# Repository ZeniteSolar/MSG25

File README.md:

# MSG25
Módulo de sensoriamento geral para medição de 4 tensões e 3 temperaturas

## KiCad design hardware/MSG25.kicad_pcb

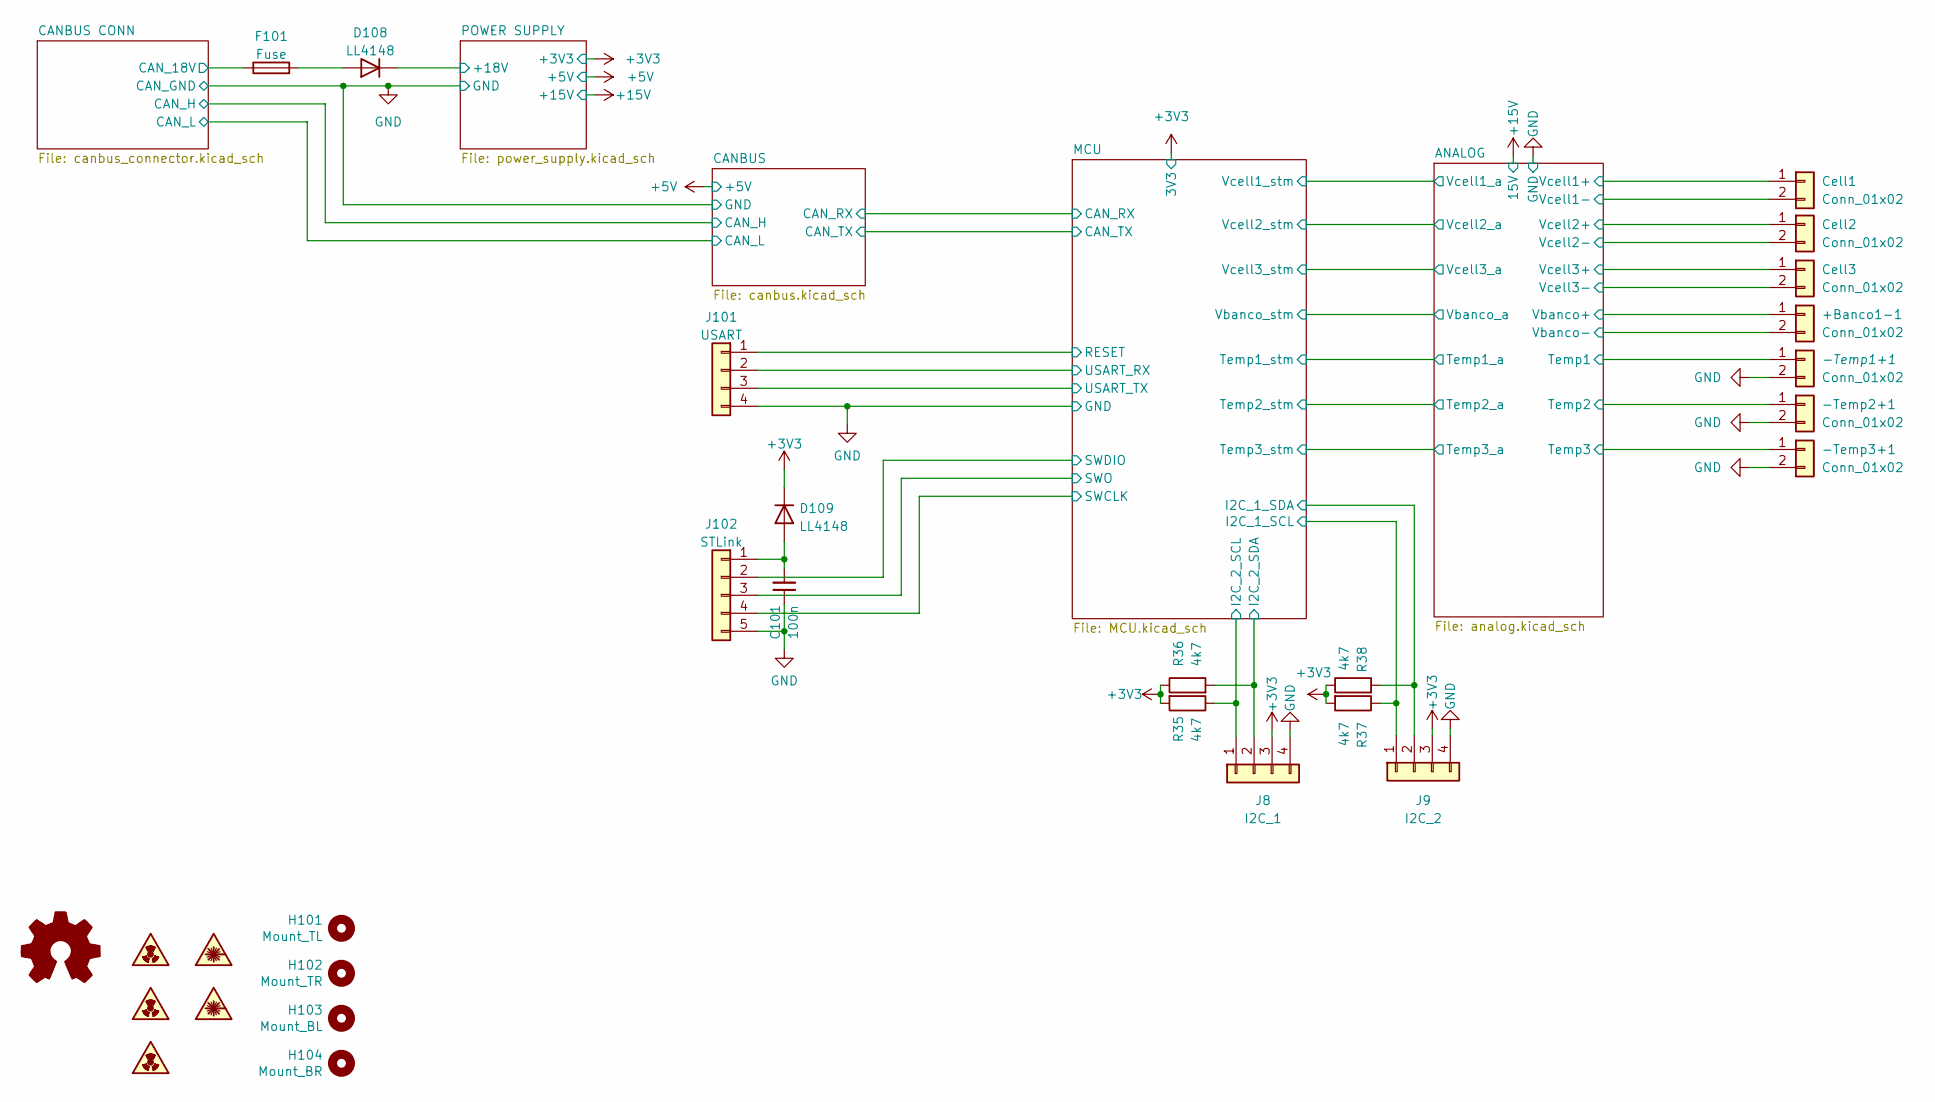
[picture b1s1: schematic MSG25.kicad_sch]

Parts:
+Banco1-1: Conn_01x02; TerminalBlock_bornier-2_P5.08mm
-Temp1+1, -Temp2+1, -Temp3+1: Conn_01x02; TerminalBlock_bornier-2_P5.08mm
C101: 100n; C_0603_1608Metric_Pad1.08x0.95mm_HandSolder
Cell1, Cell2, Cell3: Conn_01x02; TerminalBlock_bornier-2_P5.08mm
D108, D109: LL4148; D_MiniMELF
F101: Fuse; Fuse_1812_4532Metric_Pad1.30x3.40mm_HandSolder
H101: Mount_TL; MountingHole_3.2mm_M3
H102: Mount_TR; MountingHole_3.2mm_M3
H103: Mount_BL; MountingHole_3.2mm_M3
H104: Mount_BR; MountingHole_3.2mm_M3
J8: I2C_1; PinSocket_1x04_P2.54mm_Horizontal
J9: I2C_2; PinSocket_1x04_P2.54mm_Horizontal
J101: USART; PinSocket_1x04_P2.54mm_Horizontal
J102: STLink; PinSocket_1x05_P2.54mm_Vertical
LOGO101: Logo_Open_Hardware_Small; OSHW-Logo2_7.3x6mm_SilkScreen
R35, R36, R37, R38: 4k7; R_0805_2012Metric_Pad1.20x1.40mm_HandSolder
SYM101, SYM102: SYM_Radioactive_Radiation_Small; symbol_logoZenite
SYM103: SYM_Radioactive_Radiation_Small; symbol_naolavar
SYM104, SYM105: SYM_LASER_Small; synbol_logoifsc

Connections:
+3V3: D109.1 (K), J8.3, J9.3, R35.2, R36.1, R37.2, R38.1; also elsewhere on the board
/ANALOG/Temp1: -Temp1+1.1; also elsewhere on the board
/ANALOG/Temp2: -Temp2+1.1; also elsewhere on the board
/ANALOG/Temp3: -Temp3+1.1; also elsewhere on the board
/ANALOG/Vbanco+: +Banco1-1.1; also elsewhere on the board
/ANALOG/Vbanco-: +Banco1-1.2; also elsewhere on the board
/ANALOG/Vcell1+: Cell1.1; also elsewhere on the board
/ANALOG/Vcell1-: Cell1.2; also elsewhere on the board
/ANALOG/Vcell2+: Cell2.1; also elsewhere on the board
/ANALOG/Vcell2-: Cell2.2; also elsewhere on the board
/ANALOG/Vcell3+: Cell3.1; also elsewhere on the board
/ANALOG/Vcell3-: Cell3.2; also elsewhere on the board
/CANBUS CONN/CAN_18V: F101.1; also elsewhere on the board
/MCU/I2C_1_SCL: J9.1, R37.1; also elsewhere on the board
/MCU/I2C_1_SDA: J9.2, R38.2; also elsewhere on the board
/MCU/I2C_2_SCL: J8.1, R35.1; also elsewhere on the board
/MCU/I2C_2_SDA: J8.2, R36.2; also elsewhere on the board
/MCU/RESET: J101.1; also elsewhere on the board
/MCU/SWCLK: J102.4; also elsewhere on the board
/MCU/SWDIO: J102.2; also elsewhere on the board
/MCU/SWO: J102.3; also elsewhere on the board
/MCU/USART_RX: J101.2; also elsewhere on the board
/MCU/USART_TX: J101.3; also elsewhere on the board
/POWER SUPPLY/+18V: D108.1 (K); also elsewhere on the board
GND: -Temp1+1.2, -Temp2+1.2, -Temp3+1.2, C101.1, J8.4, J9.4, J101.4, J102.5; also elsewhere on the board
unnamed: D108.2 (A), F101.2
unnamed: C101.2, D109.2 (A), J102.1

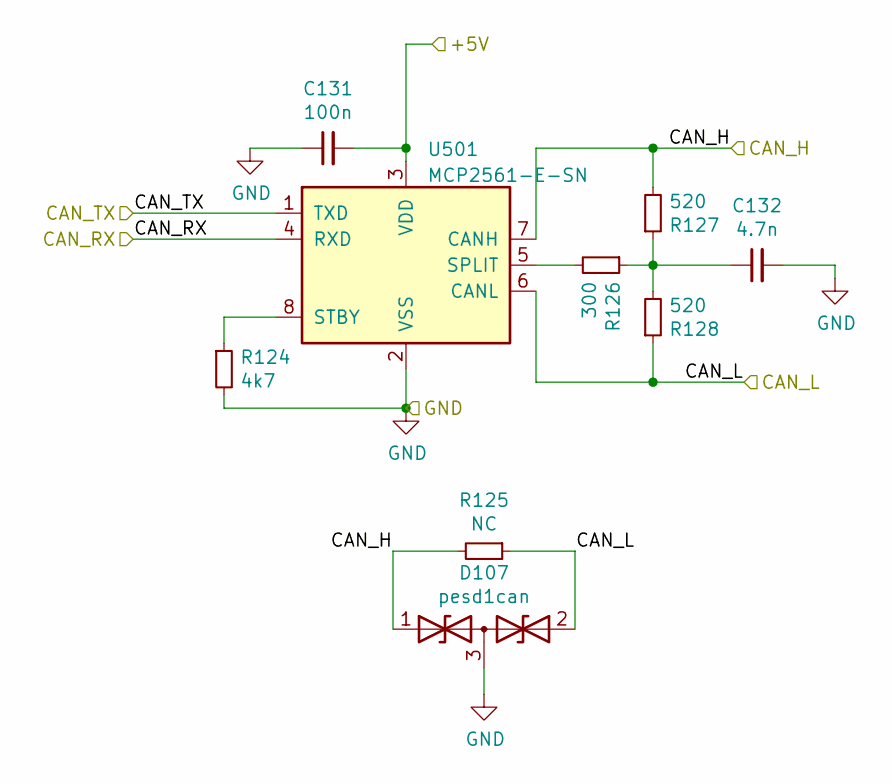
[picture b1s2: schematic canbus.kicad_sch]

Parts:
C131: 100n; C_0603_1608Metric_Pad1.08x0.95mm_HandSolder
C132: 4.7n; C_0603_1608Metric_Pad1.08x0.95mm_HandSolder
D107: pesd1can; SOT-23
R124: 4k7; R_0603_1608Metric_Pad0.98x0.95mm_HandSolder
R125: NC; R_0603_1608Metric_Pad0.98x0.95mm_HandSolder
R126: 300; R_0603_1608Metric_Pad0.98x0.95mm_HandSolder
R127, R128: 520; R_0603_1608Metric_Pad0.98x0.95mm_HandSolder
U501: MCP2561-E-SN; SOIC-8_3.9x4.9mm_P1.27mm

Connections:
+5V: C131.2, U501.3 (VDD); also elsewhere on the board
/CANBUS CONN/CAN_H: D107.1 (A1), R125.2, R127.2, U501.7 (CANH); also elsewhere on the board
/CANBUS CONN/CAN_L: D107.2 (A2), R125.1, R128.1, U501.6 (CANL); also elsewhere on the board
/CANBUS/CAN_RX: U501.4 (RXD); also elsewhere on the board
/CANBUS/CAN_TX: U501.1 (TXD); also elsewhere on the board
GND: C131.1, C132.2, D107.3 (common), R124.2, U501.2 (VSS); also elsewhere on the board
unnamed: C132.1, R126.1, R127.1, R128.2
unnamed: R126.2, U501.5 (SPLIT)
unnamed: R124.1, U501.8 (STBY)

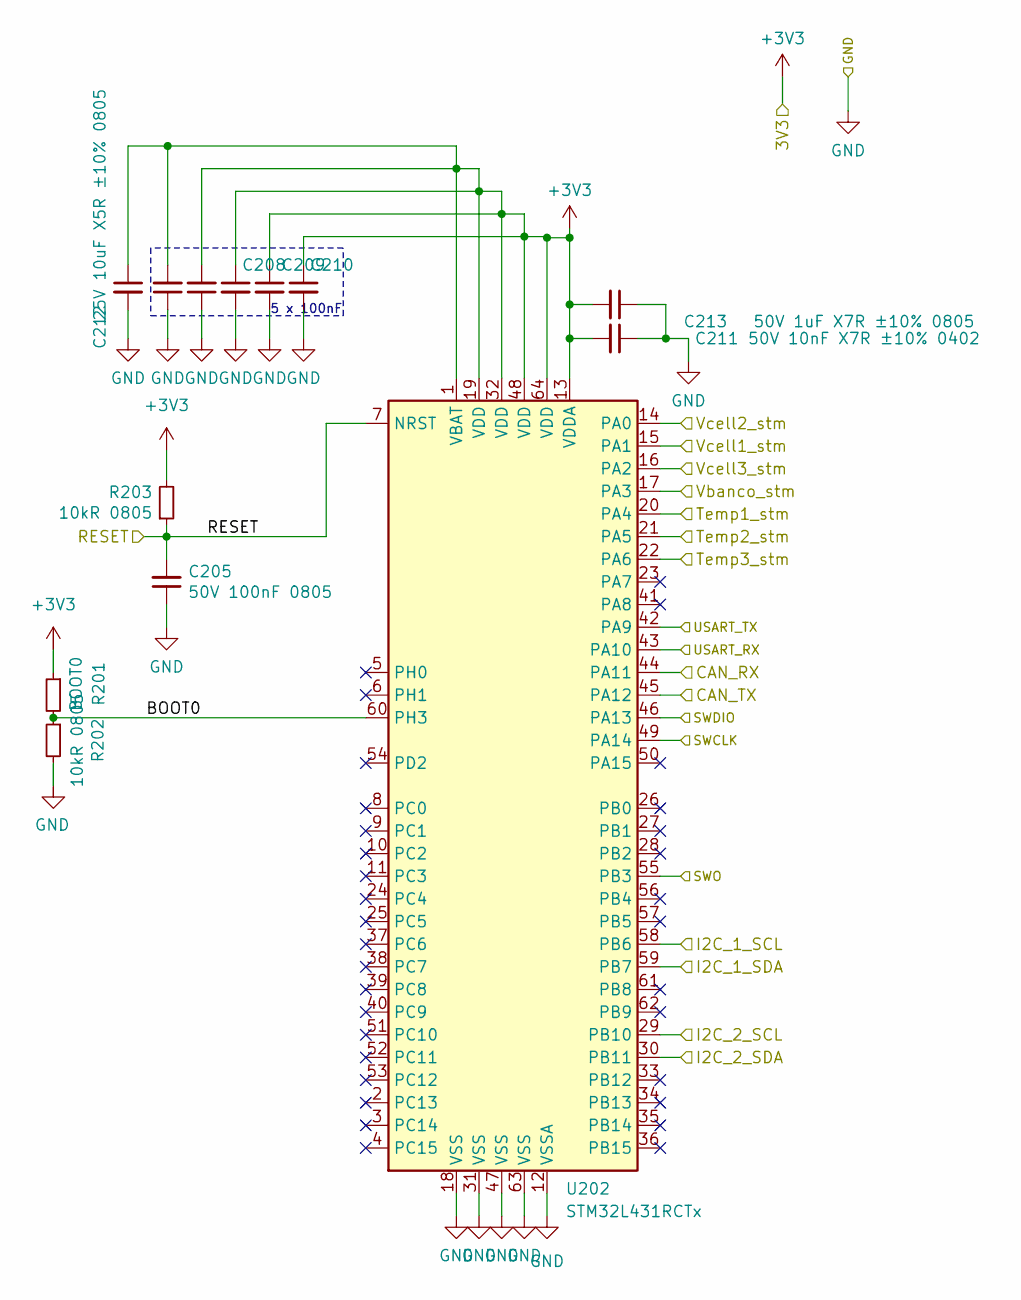
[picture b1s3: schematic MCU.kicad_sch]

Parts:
C205, C206, C207: 50V 100nF 0805; C_0805_2012Metric_Pad1.18x1.45mm_HandSolder
C208, C209, C210: 50V 100nF X7R ±10% 0402; C_0402_1005Metric_Pad0.74x0.62mm_HandSolder
C211: 50V 10nF X7R ±10% 0402; C_0402_1005Metric_Pad0.74x0.62mm_HandSolder
C212: 25V 10uF X5R ±10% 0805; C_0805_2012Metric_Pad1.18x1.45mm_HandSolder
C213: 50V 1uF X7R ±10% 0805; C_0805_2012Metric_Pad1.18x1.45mm_HandSolder
R201: BOOT0; R_0402_1005Metric
R202, R203: 10kR 0805; R_0805_2012Metric_Pad1.20x1.40mm_HandSolder
U202: STM32L431RCTx; LQFP-64_10x10mm_P0.5mm

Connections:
+3V3: C206.2, C207.2, C208.1, C209.1, C210.1, C211.2, C212.1, C213.2, R201.1, R203.2, U202.1 (VBAT), U202.13 (VDDA), U202.19 (VDD), U202.32 (VDD), U202.48 (VDD), U202.64 (VDD); also elsewhere on the board
/ANALOG/Temp1_a: U202.20 (PA4); also elsewhere on the board
/ANALOG/Temp2_a: U202.21 (PA5); also elsewhere on the board
/ANALOG/Temp3_a: U202.22 (PA6); also elsewhere on the board
/ANALOG/Vbanco_a: U202.17 (PA3); also elsewhere on the board
/ANALOG/Vcell1_a: U202.15 (PA1); also elsewhere on the board
/ANALOG/Vcell2_a: U202.14 (PA0); also elsewhere on the board
/ANALOG/Vcell3_a: U202.16 (PA2); also elsewhere on the board
/CANBUS/CAN_RX: U202.44 (PA11); also elsewhere on the board
/CANBUS/CAN_TX: U202.45 (PA12); also elsewhere on the board
/MCU/BOOT0: R201.2, R202.1, U202.60 (PH3)
/MCU/I2C_1_SCL: U202.58 (PB6); also elsewhere on the board
/MCU/I2C_1_SDA: U202.59 (PB7); also elsewhere on the board
/MCU/I2C_2_SCL: U202.29 (PB10); also elsewhere on the board
/MCU/I2C_2_SDA: U202.30 (PB11); also elsewhere on the board
/MCU/RESET: C205.2, R203.1, U202.7 (NRST); also elsewhere on the board
/MCU/SWCLK: U202.49 (PA14); also elsewhere on the board
/MCU/SWDIO: U202.46 (PA13); also elsewhere on the board
/MCU/SWO: U202.55 (PB3); also elsewhere on the board
/MCU/USART_RX: U202.43 (PA10); also elsewhere on the board
/MCU/USART_TX: U202.42 (PA9); also elsewhere on the board
GND: C205.1, C206.1, C207.1, C208.2, C209.2, C210.2, C211.1, C212.2, C213.1, R202.2, U202.12 (VSSA), U202.18 (VSS), U202.31 (VSS), U202.47 (VSS), U202.63 (VSS); also elsewhere on the board

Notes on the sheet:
5 x 100nF

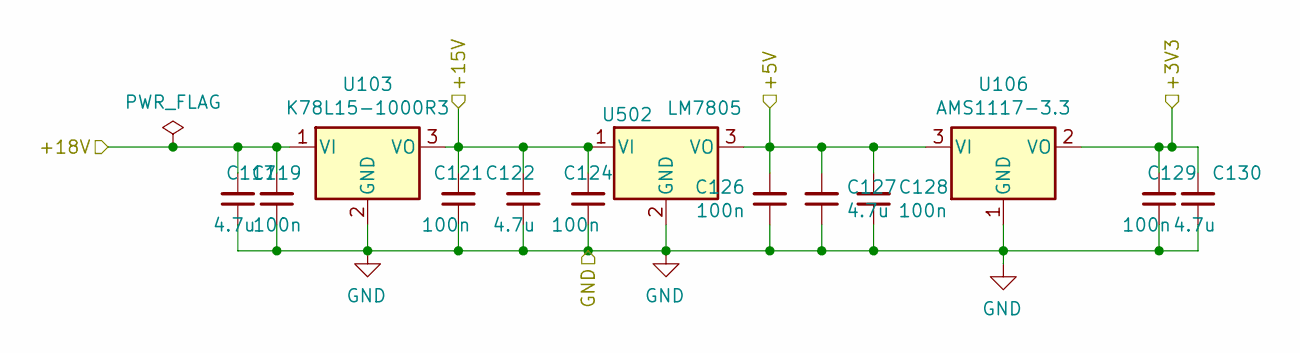
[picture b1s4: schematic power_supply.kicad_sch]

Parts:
C117, C122, C127, C130: 4.7u; C_1206_3216Metric_Pad1.33x1.80mm_HandSolder
C119, C121, C124, C126, C128, C129: 100n; C_0603_1608Metric_Pad1.08x0.95mm_HandSolder
U103: K78L15-1000R3; TO-220-3_Horizontal_TabDown
U106: AMS1117-3.3; SOT-223-3_TabPin2
U502: LM7805; TO-220-3_Horizontal_TabDown

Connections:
+3V3: C129.2, C130.2, U106.2 (VO); also elsewhere on the board
+5V: C126.2, C127.2, C128.2, U106.3 (VI), U502.3 (VO); also elsewhere on the board
+15V: C121.2, C122.2, C124.2, U103.3 (VO), U502.1 (VI); also elsewhere on the board
/POWER SUPPLY/+18V: C117.2, C119.2, U103.1 (VI); also elsewhere on the board
GND: C117.1, C119.1, C121.1, C122.1, C124.1, C126.1, C127.1, C128.1, C129.1, C130.1, U103.2 (GND), U106.1 (GND), U502.2 (GND); also elsewhere on the board

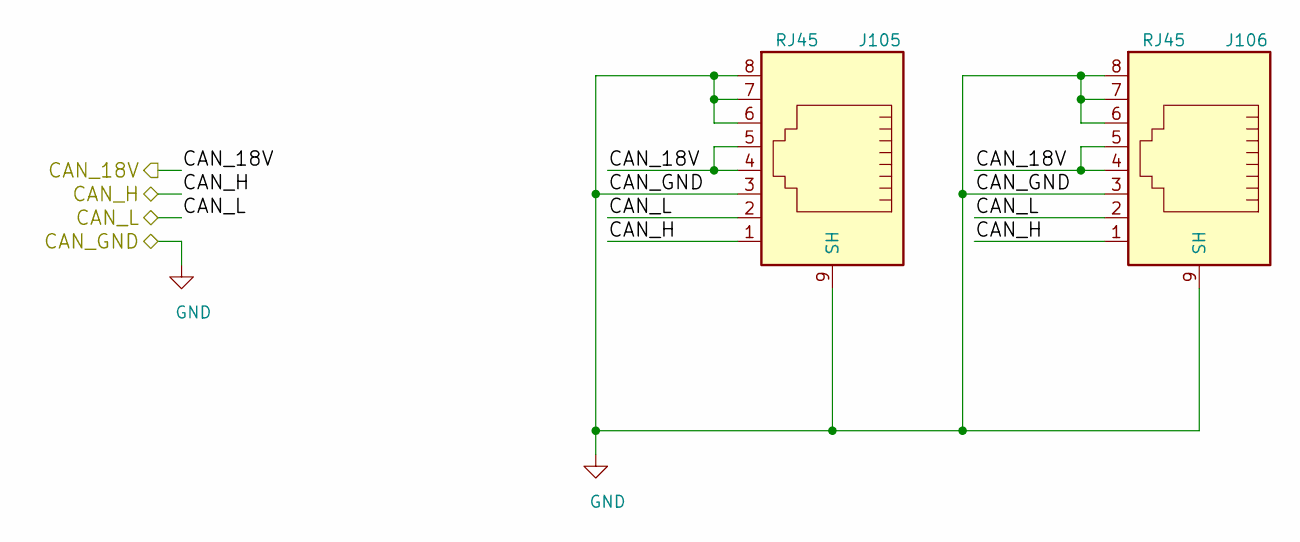
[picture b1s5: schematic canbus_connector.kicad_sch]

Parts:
J105, J106: RJ45; RJ45_YH59_01

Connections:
/CANBUS CONN/CAN_18V: J105.4, J105.5, J106.4, J106.5; also elsewhere on the board
/CANBUS CONN/CAN_H: J105.1, J106.1; also elsewhere on the board
/CANBUS CONN/CAN_L: J105.2, J106.2; also elsewhere on the board
GND: J105.3, J105.6, J105.7, J105.8, J105.9 (SH), J106.3, J106.6, J106.7, J106.8, J106.9 (SH); also elsewhere on the board

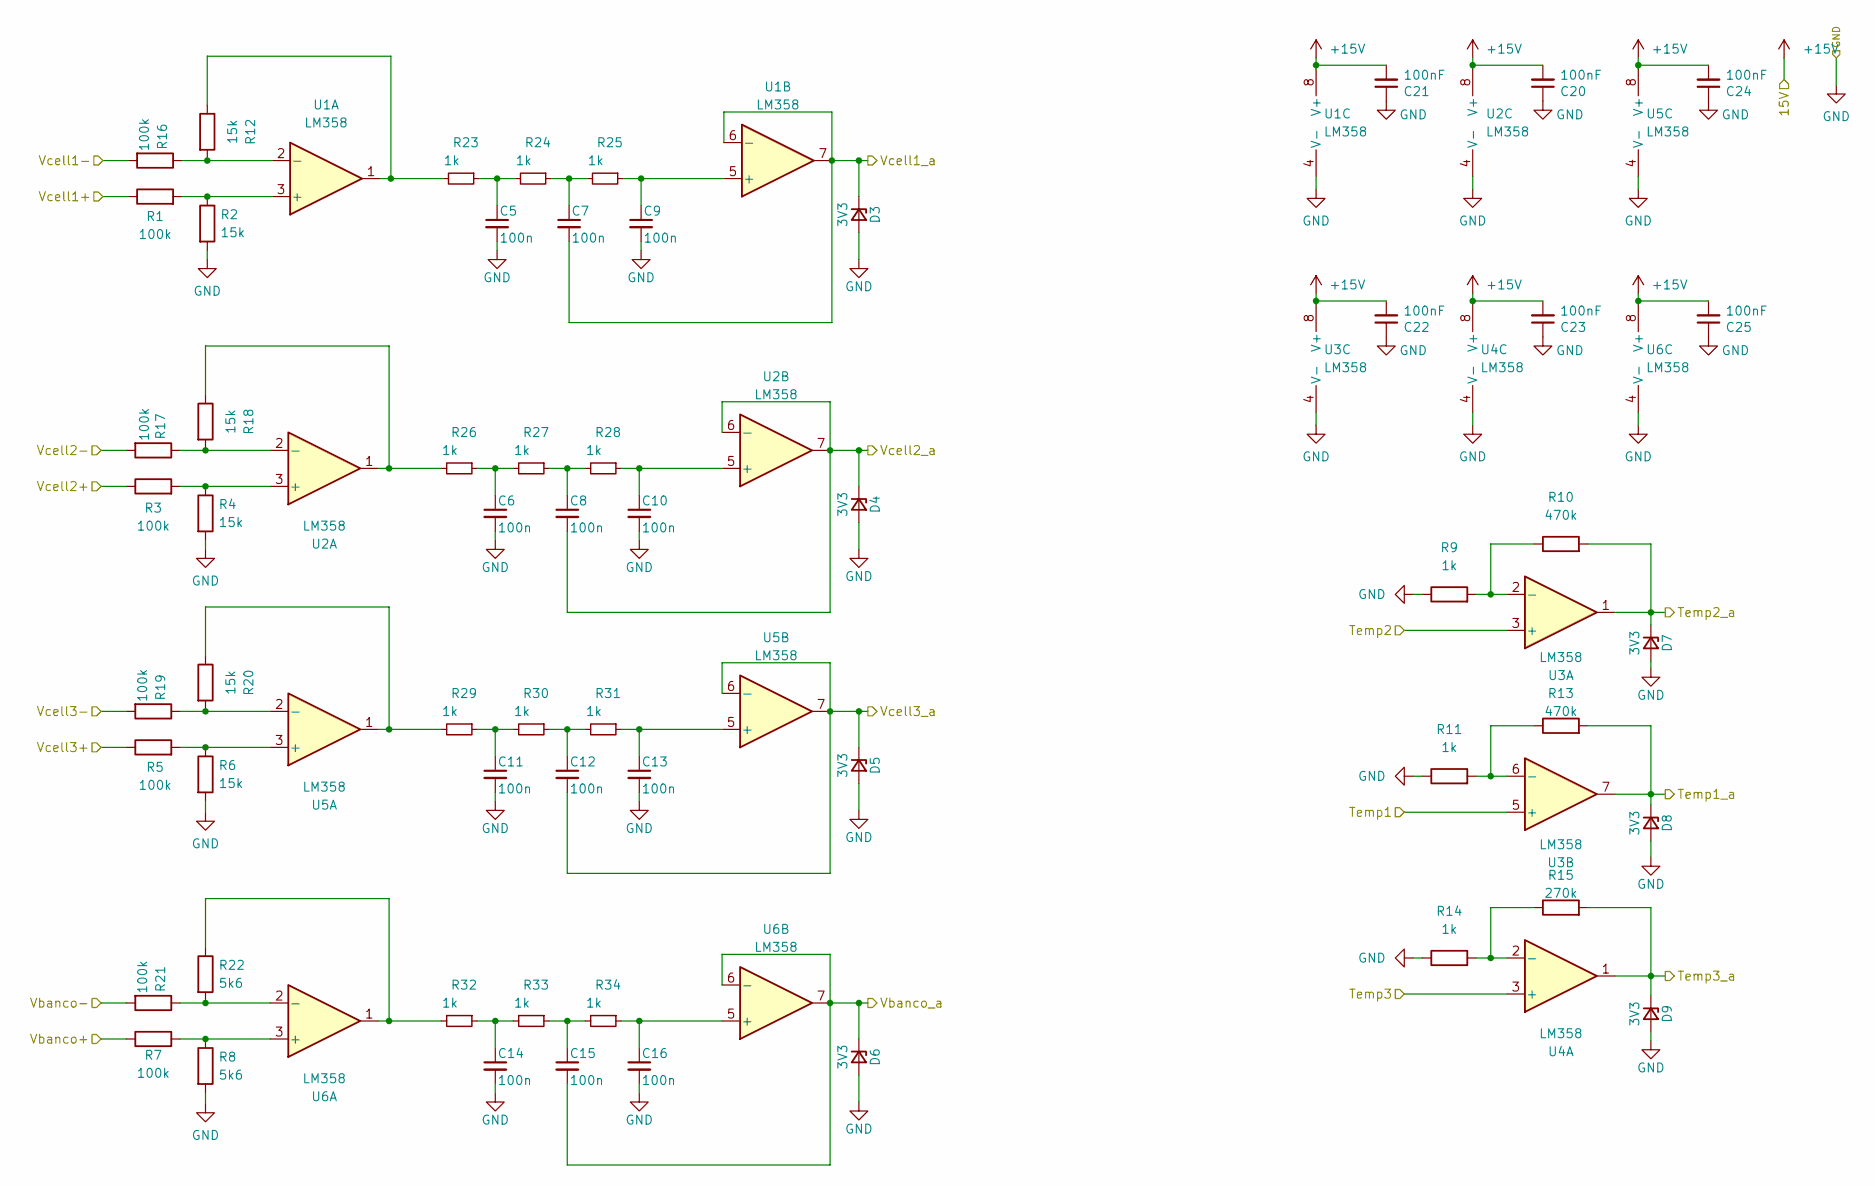
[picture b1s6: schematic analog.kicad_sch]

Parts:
C5, C6, C7, C8, C9, C10, C11, C12, C13, C14, C15, C16: 100n; C_0805_2012Metric_Pad1.18x1.45mm_HandSolder
C20, C21, C22, C23, C24, C25: 100nF; C_0805_2012Metric_Pad1.18x1.45mm_HandSolder
D3, D4, D5, D6, D7, D8, D9: 3V3; D_MiniMELF
R1, R3, R5, R7, R16, R17, R19, R21: 100k; R_0805_2012Metric_Pad1.20x1.40mm_HandSolder
R2, R4, R6, R12, R18, R20: 15k; R_0805_2012Metric_Pad1.20x1.40mm_HandSolder
R8, R22: 5k6; R_0805_2012Metric_Pad1.20x1.40mm_HandSolder
R9, R11, R14, R23, R24, R25, R26, R27, R28, R29, R30, R31, R32, R33, R34: 1k; R_0805_2012Metric_Pad1.20x1.40mm_HandSolder
R10, R13: 470k; R_0805_2012Metric_Pad1.20x1.40mm_HandSolder
R15: 270k; R_0805_2012Metric_Pad1.20x1.40mm_HandSolder
U1, U2, U3, U4, U5, U6: LM358; SOIC-8_3.9x4.9mm_P1.27mm

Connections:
+15V: C20.2, C21.2, C22.2, C23.2, C24.2, C25.2, U1.8 (V+), U2.8 (V+), U3.8 (V+), U4.8 (V+), U5.8 (V+), U6.8 (V+); also elsewhere on the board
/ANALOG/Temp1: U3.5 (+); also elsewhere on the board
/ANALOG/Temp1_a: D8.1 (K), R13.2, U3.7; also elsewhere on the board
/ANALOG/Temp2: U3.3 (+); also elsewhere on the board
/ANALOG/Temp2_a: D7.1 (K), R10.2, U3.1; also elsewhere on the board
/ANALOG/Temp3: U4.3 (+); also elsewhere on the board
/ANALOG/Temp3_a: D9.1 (K), R15.2, U4.1; also elsewhere on the board
/ANALOG/Vbanco+: R7.1; also elsewhere on the board
/ANALOG/Vbanco-: R21.2; also elsewhere on the board
/ANALOG/Vbanco_a: C15.2, D6.1 (K), U6.6 (-), U6.7; also elsewhere on the board
/ANALOG/Vcell1+: R1.1; also elsewhere on the board
/ANALOG/Vcell1-: R16.2; also elsewhere on the board
/ANALOG/Vcell1_a: C7.2, D3.1 (K), U1.6 (-), U1.7; also elsewhere on the board
/ANALOG/Vcell2+: R3.1; also elsewhere on the board
/ANALOG/Vcell2-: R17.2; also elsewhere on the board
/ANALOG/Vcell2_a: C8.2, D4.1 (K), U2.6 (-), U2.7; also elsewhere on the board
/ANALOG/Vcell3+: R5.1; also elsewhere on the board
/ANALOG/Vcell3-: R19.2; also elsewhere on the board
/ANALOG/Vcell3_a: C12.2, D5.1 (K), U5.6 (-), U5.7; also elsewhere on the board
GND: C5.2, C6.2, C9.2, C10.2, C11.2, C13.2, C14.2, C16.2, C20.1, C21.1, C22.1, C23.1, C24.1, C25.1, D3.2 (A), D4.2 (A), D5.2 (A), D6.2 (A), D7.2 (A), D8.2 (A), D9.2 (A), R2.2, R4.2, R6.2, R8.2, R9.1, R11.1, R14.1, U1.4 (V-), U2.4 (V-), U3.4 (V-), U4.4 (V-), U5.4 (V-), U6.4 (V-); also elsewhere on the board
unnamed: C5.1, R23.1, R24.2
unnamed: C6.1, R26.1, R27.2
unnamed: C7.1, R24.1, R25.2
unnamed: C8.1, R27.1, R28.2
unnamed: C11.1, R29.1, R30.2
unnamed: C12.1, R30.1, R31.2
unnamed: C14.1, R32.1, R33.2
unnamed: C15.1, R33.1, R34.2
unnamed: R12.1, R23.2, U1.1
unnamed: R18.1, R26.2, U2.1
unnamed: R20.1, R29.2, U5.1
unnamed: R22.1, R32.2, U6.1
unnamed: R1.2, R2.1, U1.3 (+)
unnamed: R12.2, R16.1, U1.2 (-)
unnamed: C9.1, R25.1, U1.5 (+)
unnamed: R3.2, R4.1, U2.3 (+)
unnamed: R17.1, R18.2, U2.2 (-)
unnamed: C10.1, R28.1, U2.5 (+)
unnamed: R9.2, R10.1, U3.2 (-)
unnamed: R11.2, R13.1, U3.6 (-)
unnamed: R14.2, R15.1, U4.2 (-)
unnamed: R5.2, R6.1, U5.3 (+)
unnamed: R19.1, R20.2, U5.2 (-)
unnamed: C13.1, R31.1, U5.5 (+)
unnamed: R7.2, R8.1, U6.3 (+)
unnamed: R21.1, R22.2, U6.2 (-)
unnamed: C16.1, R34.1, U6.5 (+)

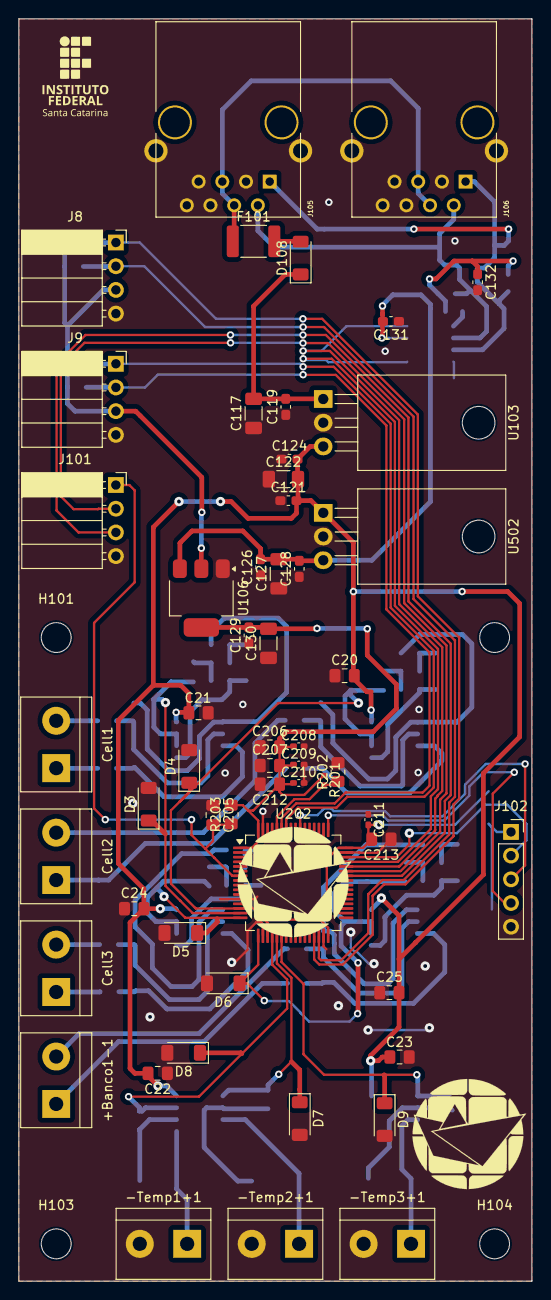
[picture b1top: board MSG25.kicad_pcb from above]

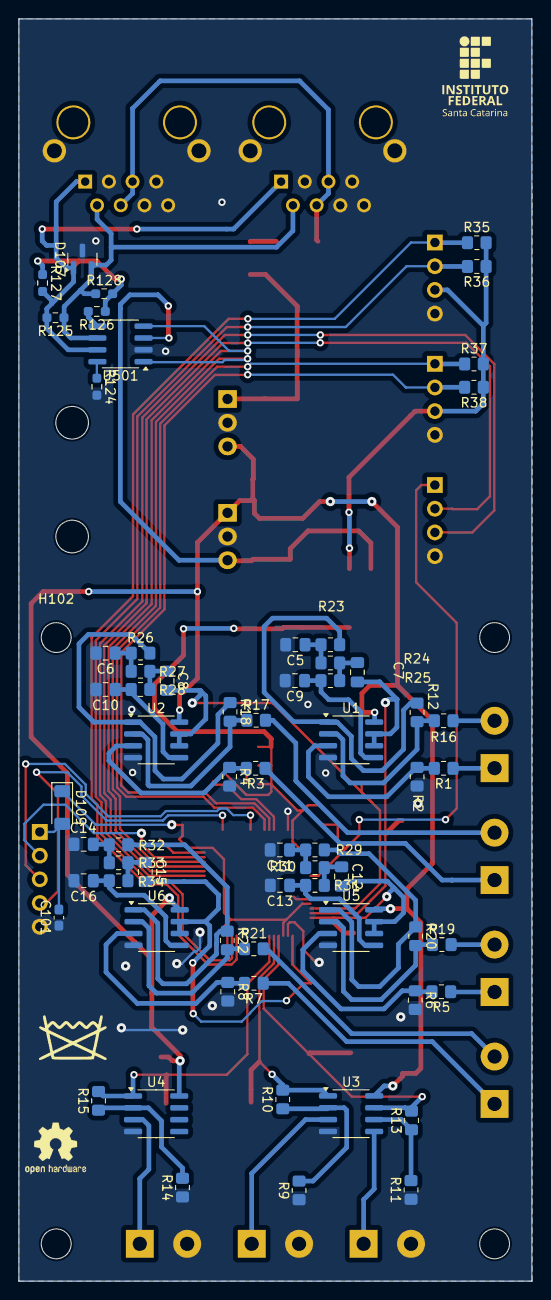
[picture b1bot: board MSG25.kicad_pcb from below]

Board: 2 copper layers, 55.0 x 135.3 mm, 131 parts (69 on the bottom side), 71 nets.

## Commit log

2025-05-09 Adicionando arquivos do projeto
2025-05-21 Atualização analog
2025-05-30 Placa Finalizada para revisão
